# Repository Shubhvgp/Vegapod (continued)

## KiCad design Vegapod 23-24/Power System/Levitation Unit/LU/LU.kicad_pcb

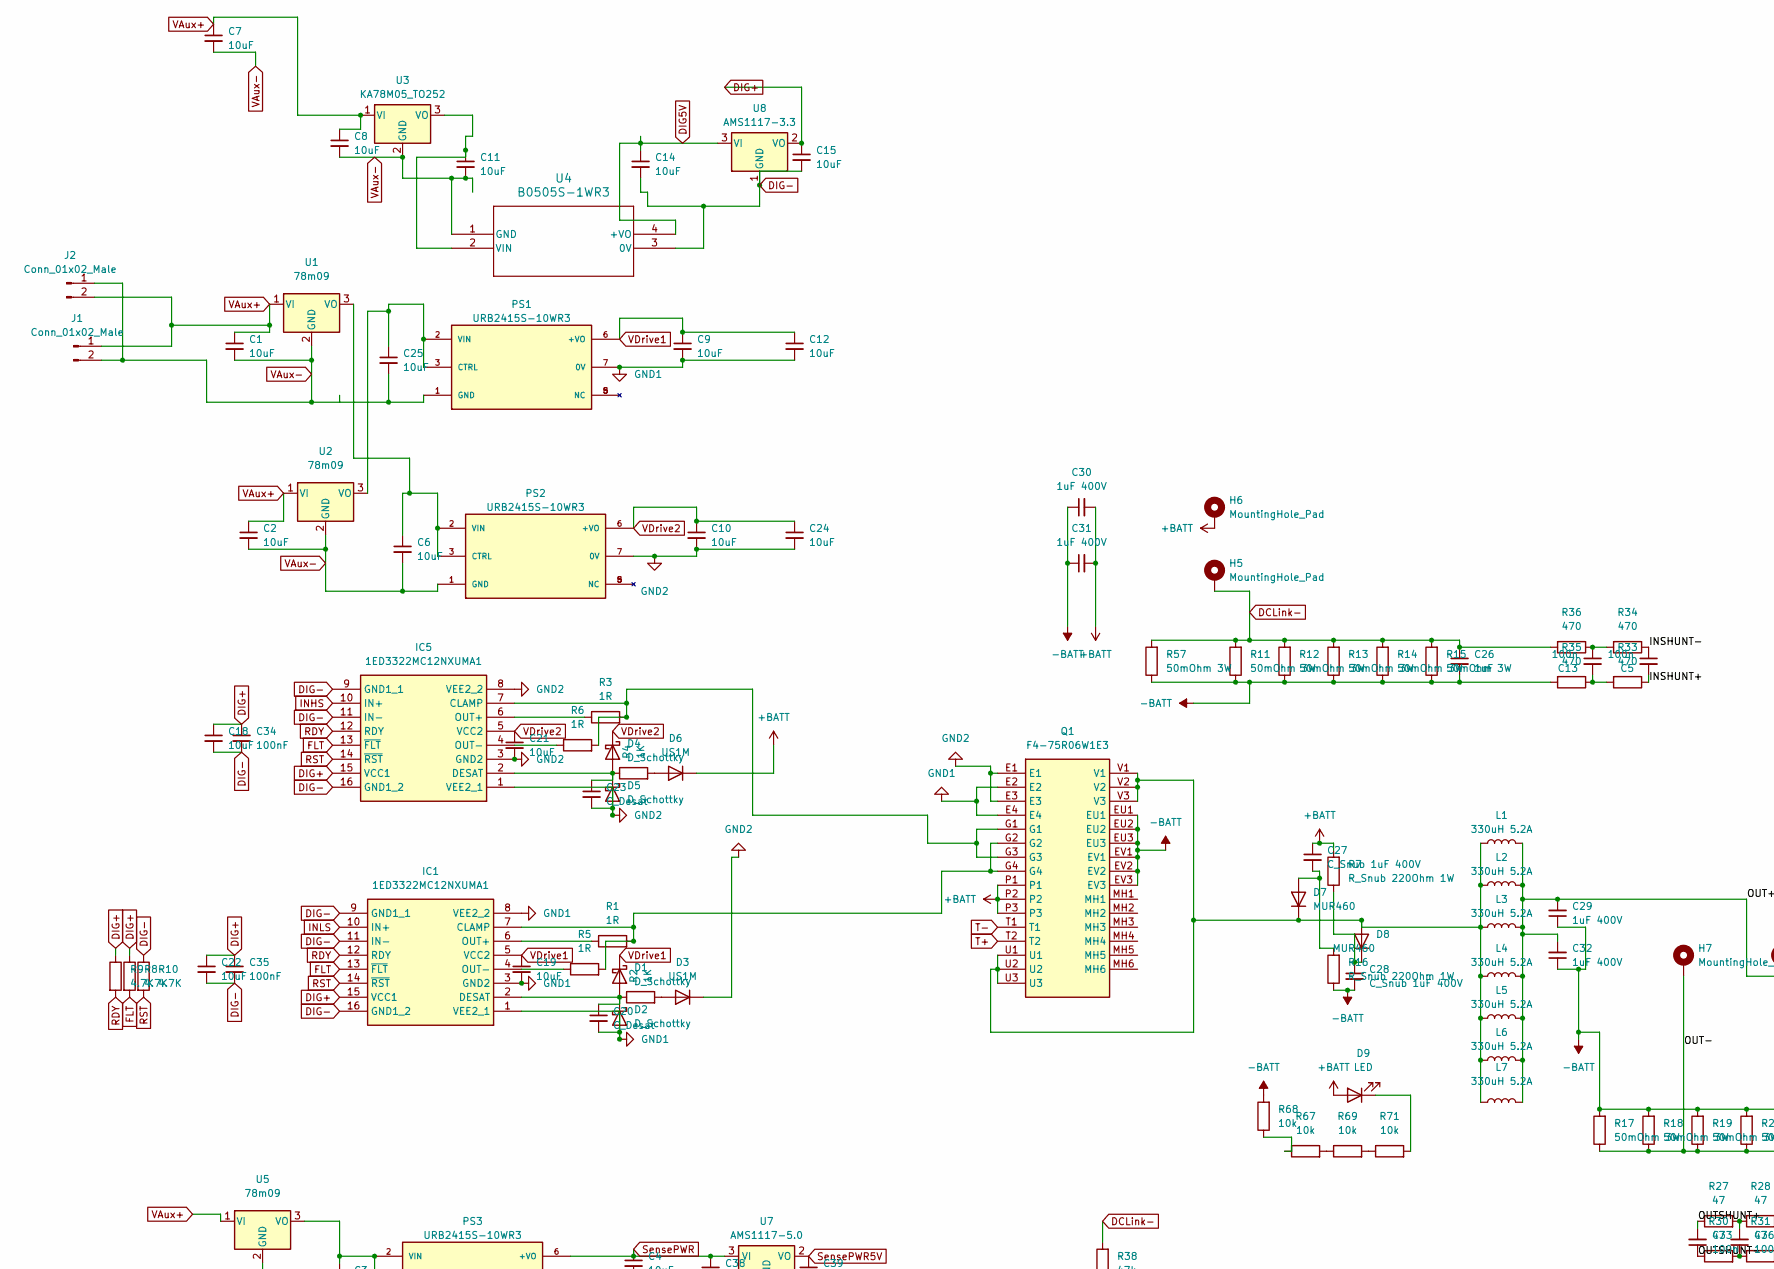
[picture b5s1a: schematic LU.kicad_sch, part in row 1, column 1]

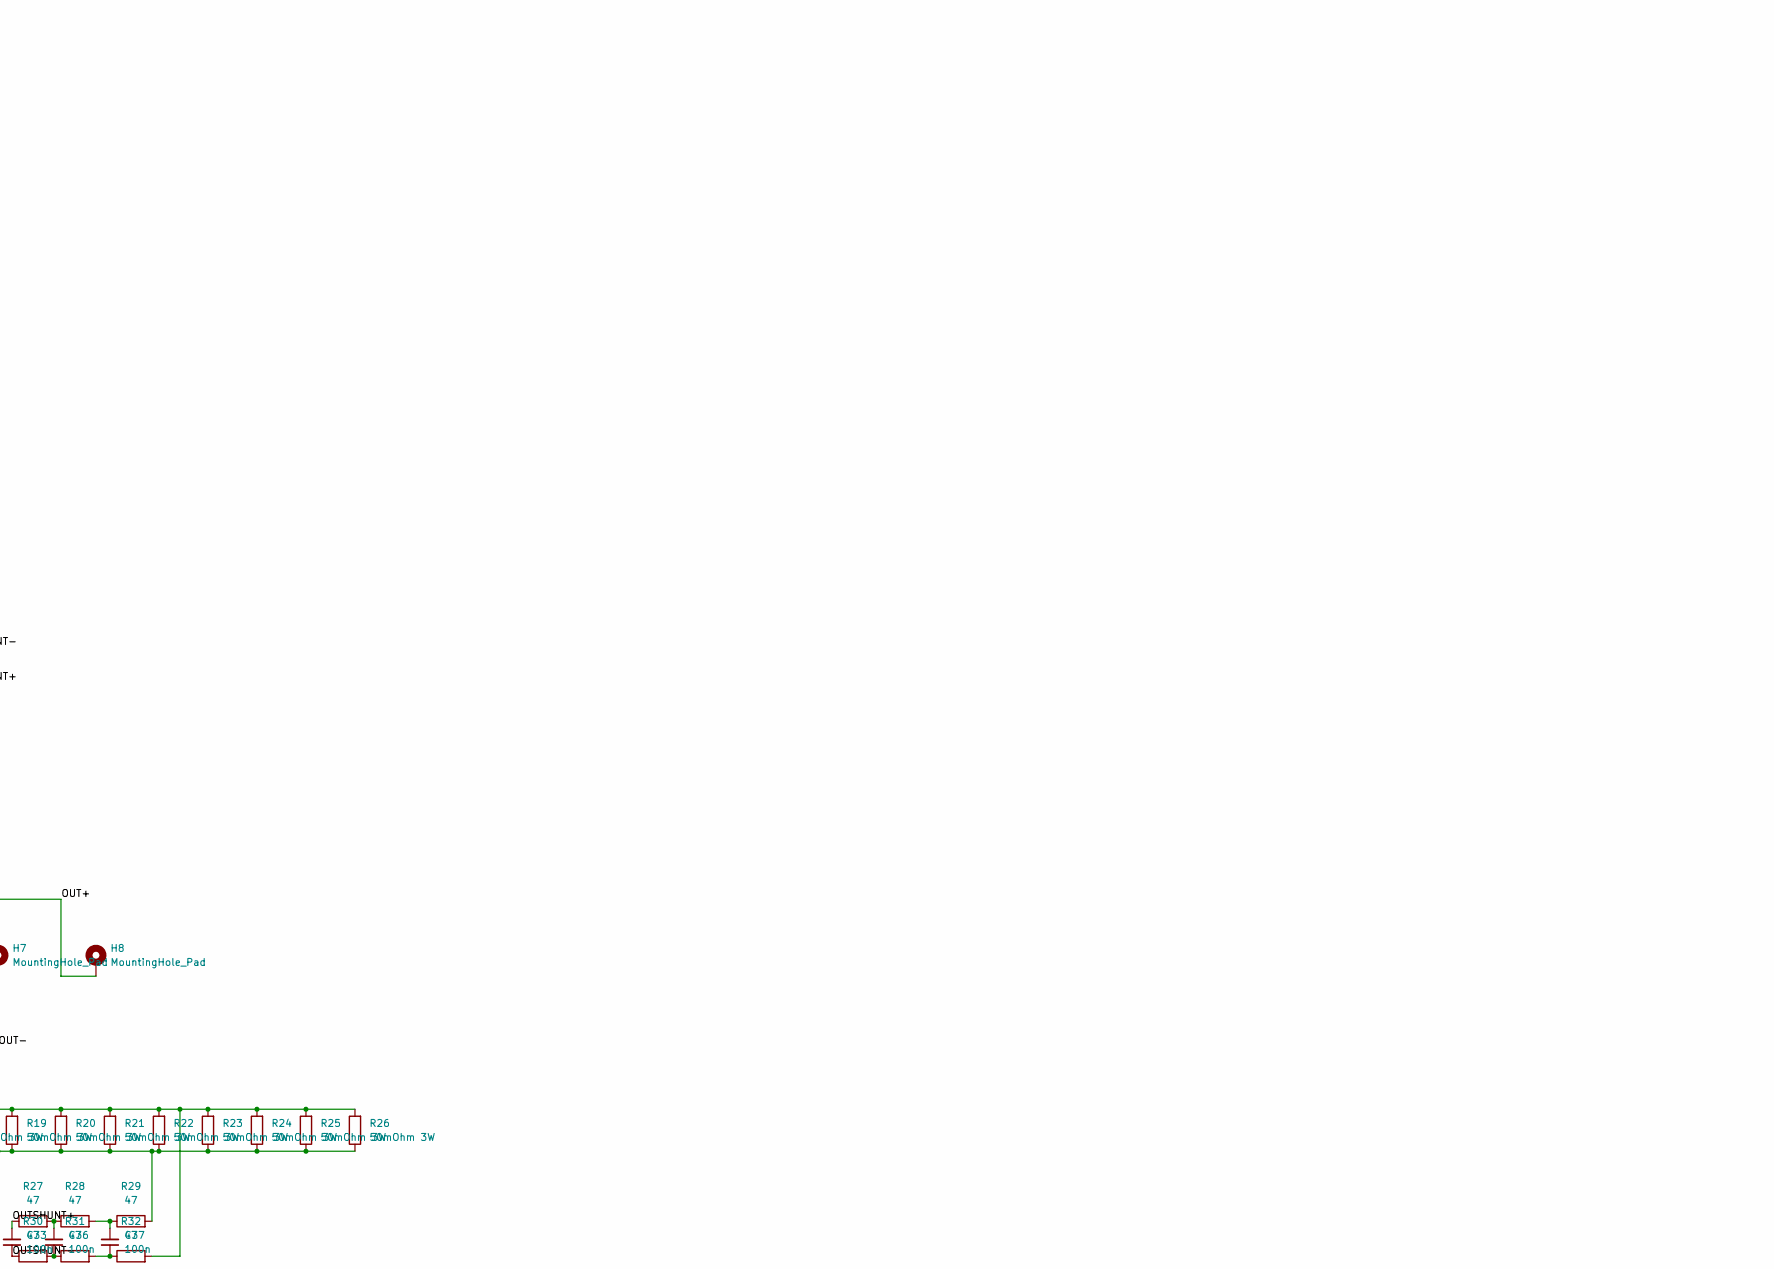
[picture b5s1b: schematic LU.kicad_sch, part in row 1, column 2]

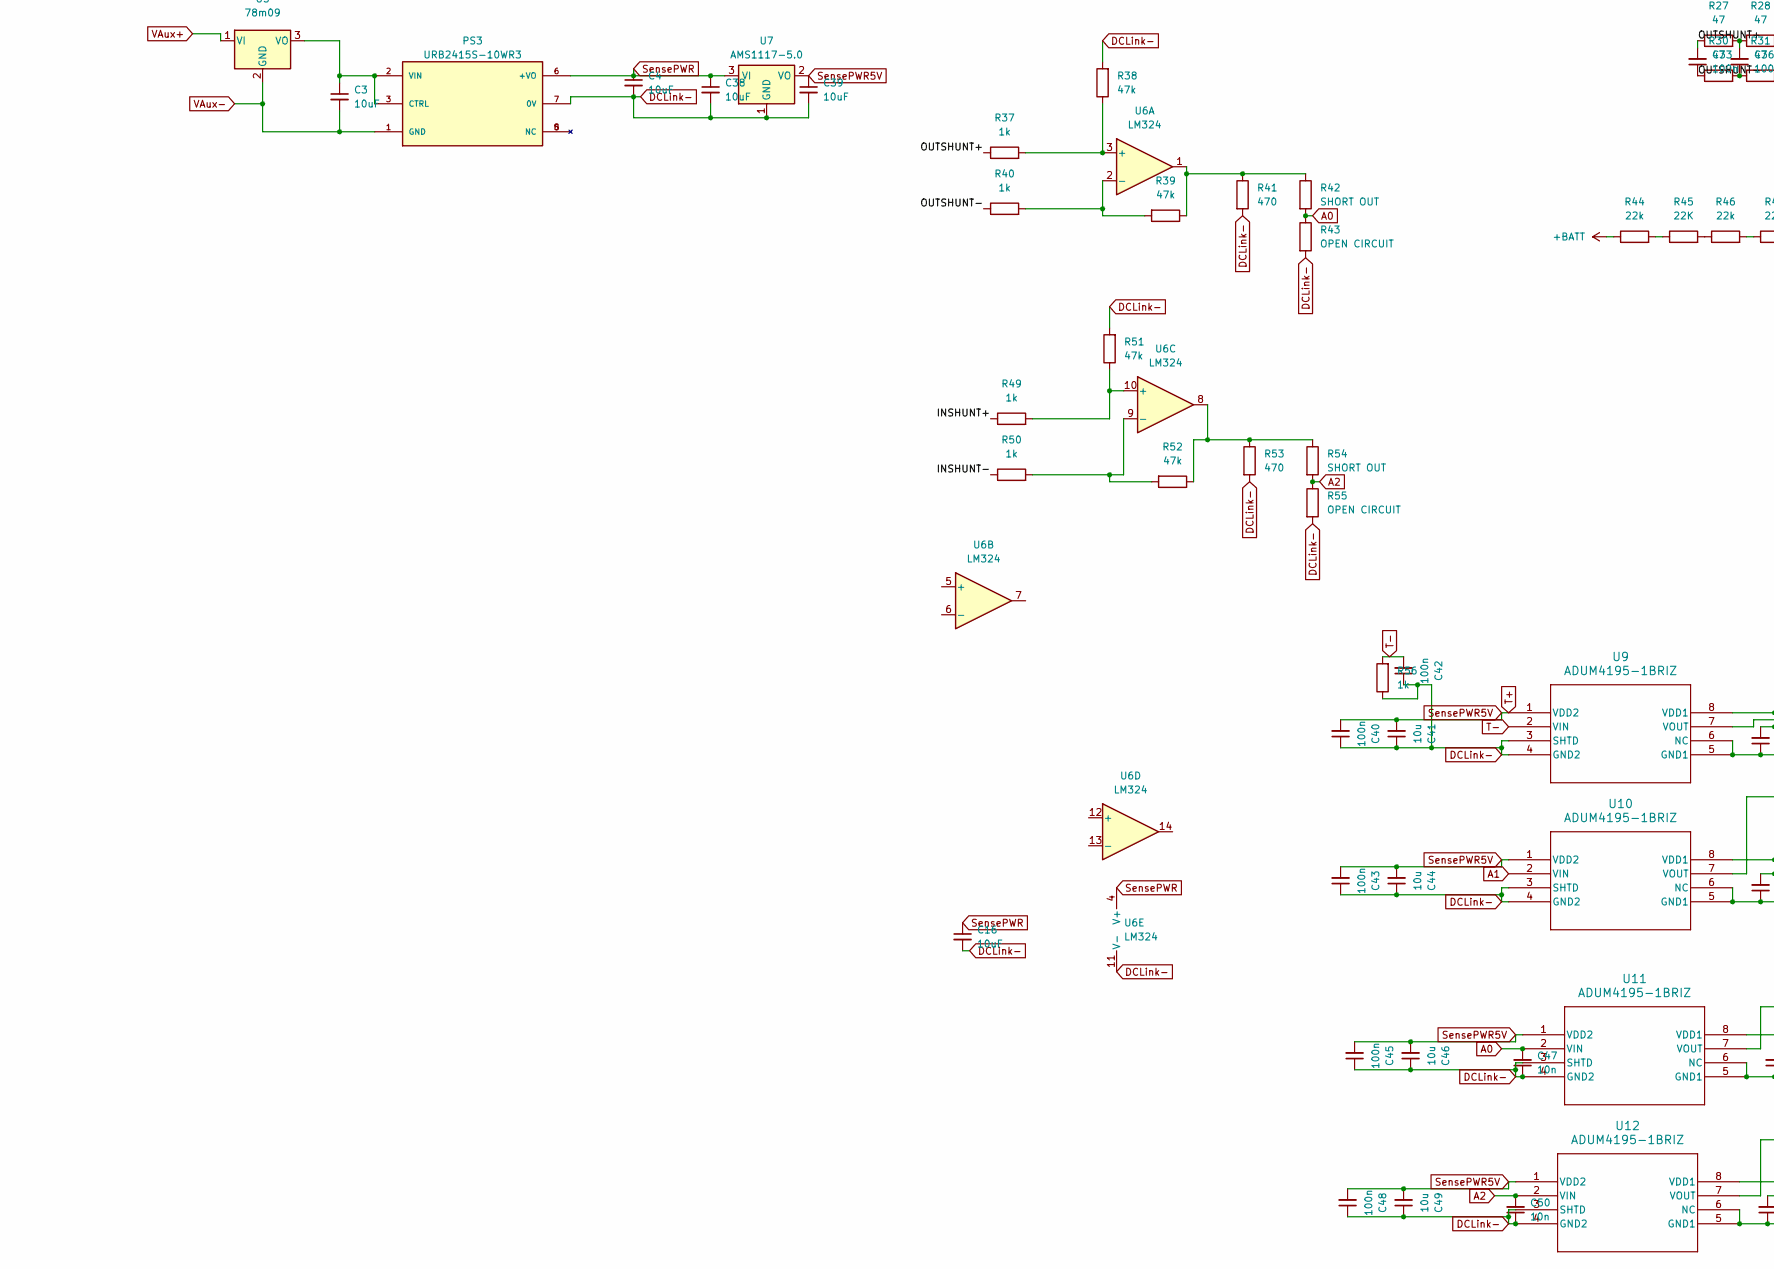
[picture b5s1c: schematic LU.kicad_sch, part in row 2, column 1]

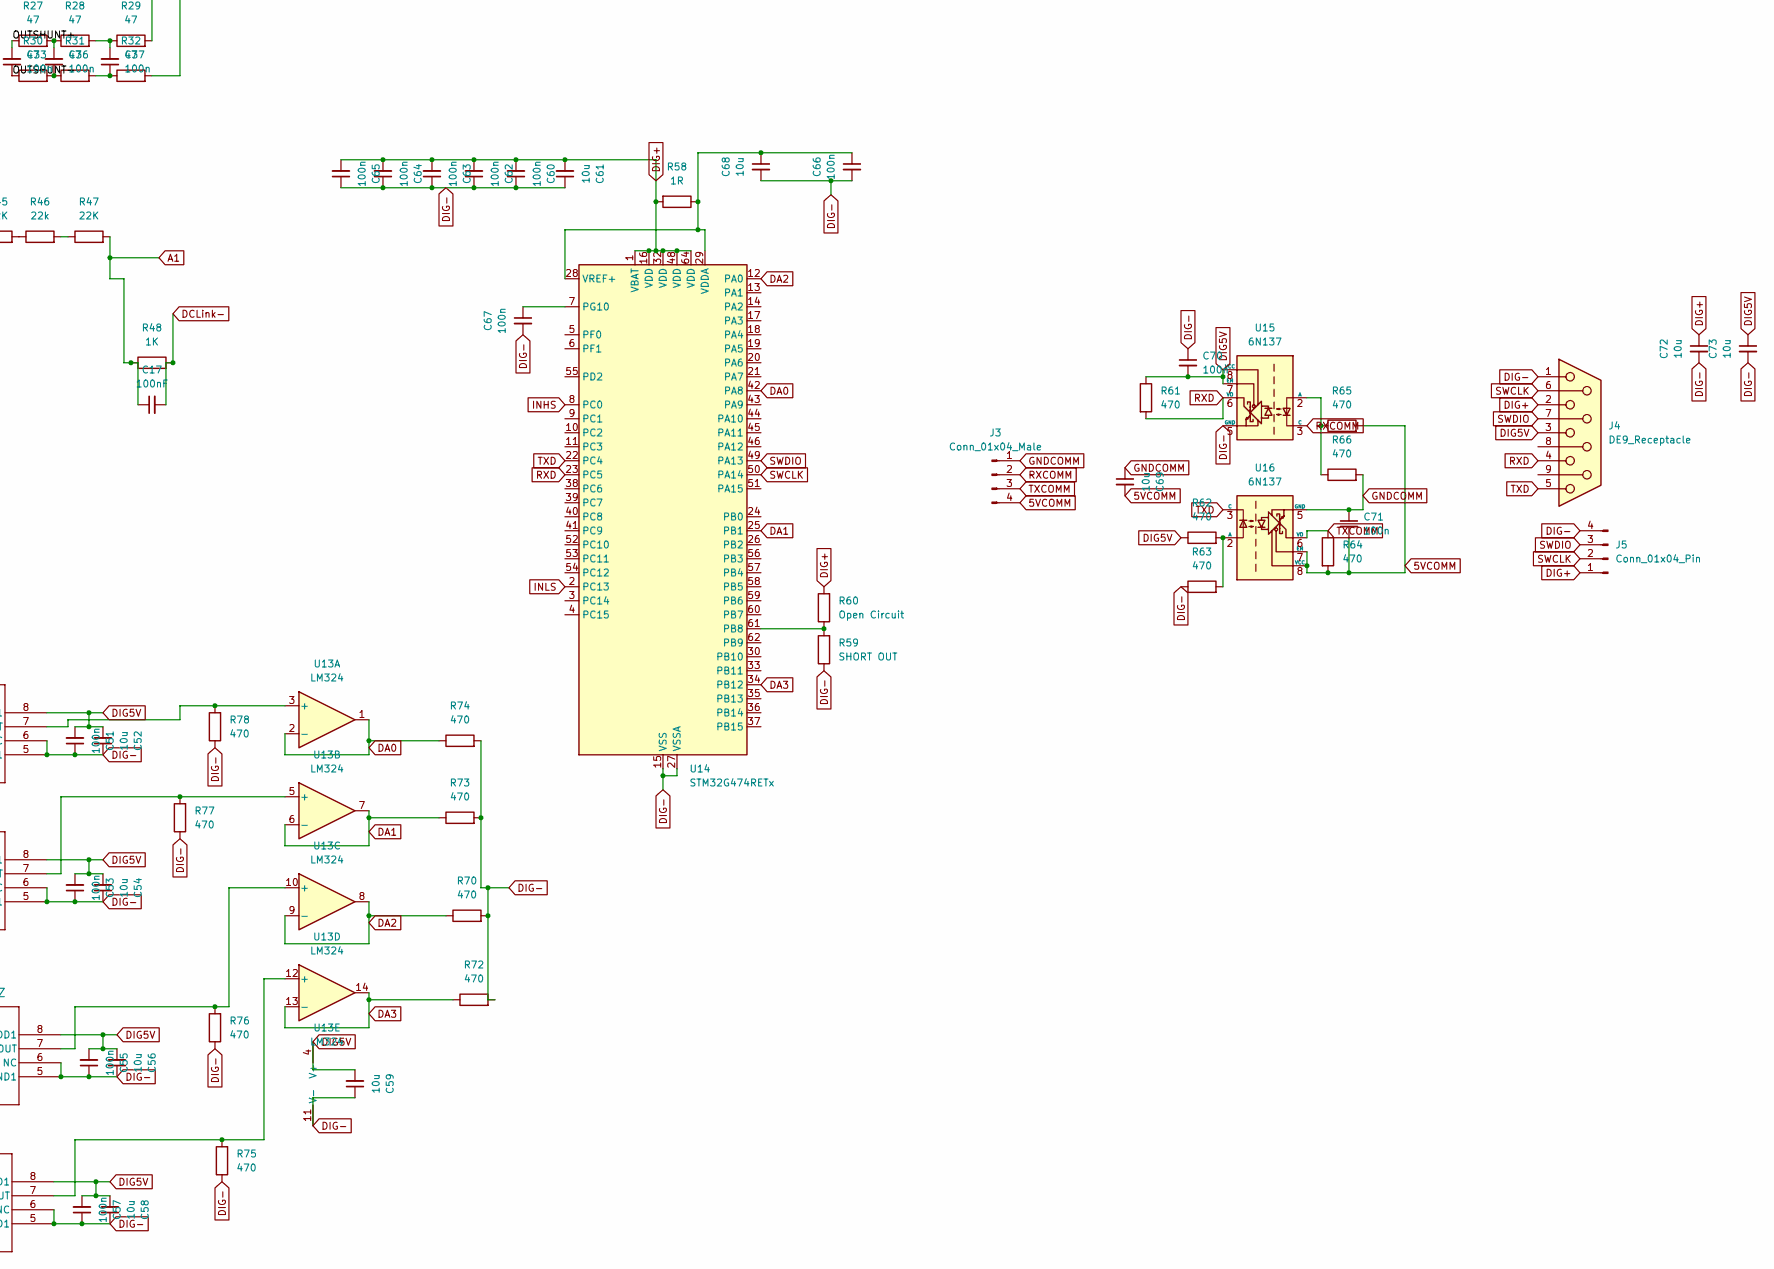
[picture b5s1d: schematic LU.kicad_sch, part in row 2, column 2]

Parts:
C1, C2, C3, C4, C6, C7, C8, C9, C10, C11, C12, C14, C15, C16, C18, C19, C21, C22, C24, C25, C38, C39: 10uF; C_1206_3216Metric_Pad1.33x1.80mm_HandSolder
C5, C13, C33, C36, C37, C40, C42, C43, C45, C48, C51, C53, C55, C57, C60, C62, C63, C64, C65, C66, C67, C70, C71: 100n; C_0805_2012Metric_Pad1.18x1.45mm_HandSolder
C17: 100nF; C_0805_2012Metric_Pad1.18x1.45mm_HandSolder
C20, C23: C_Desat; C_0603_1608Metric_Pad1.08x0.95mm_HandSolder
C26: 1uF; C_1206_3216Metric_Pad1.33x1.80mm_HandSolder
C27, C28: C_Snub 1uF 400V; C_Rect_L24.0mm_W8.3mm_P22.50mm_MKT
C29, C32: 1uF 400V; C_Rect_L19.0mm_W9.0mm_P15.00mm_MKS4
C30, C31: 1uF 400V; C_Rect_L24.0mm_W8.3mm_P22.50mm_MKT
C34, C35: 100nF; C_0603_1608Metric_Pad1.08x0.95mm_HandSolder
C41, C44, C46, C49, C52, C54, C56, C58, C59, C61, C68, C69, C72, C73: 10u; C_1206_3216Metric_Pad1.33x1.80mm_HandSolder
C47, C50: 10n; C_0805_2012Metric_Pad1.18x1.45mm_HandSolder
D1, D2, D4, D5: D_Schottky; D_SMA_Handsoldering
D3, D6: US1M; D_SMA_Handsoldering
D7, D8: MUR460; D_DO-201AE_P15.24mm_Horizontal
D9: LED; D_0805_2012Metric_Pad1.15x1.40mm_HandSolder
H5, H6: MountingHole_Pad; MountingHole_6.4mm_M6_DIN965_Pad
H7, H8: MountingHole_Pad; MountingHole_2.2mm_M2_DIN965_Pad
IC1, IC5: 1ED3322MC12NXUMA1; SOIC127P1030X265-16N; Mouser Part Number 726-1ED3322MC12NXUMA
J1: Conn_01x02_Male; JST_XH_B2B-XH-A_1x02_P2.50mm_Vertical
J2: Conn_01x02_Male; PinSocket_1x02_P2.54mm_Vertical
J3: Conn_01x04_Male; PinHeader_1x04_P2.54mm_Vertical
J4: DE9_Receptacle; DSUB-9_Male_Vertical_P2.77x2.84mm
J5: Conn_01x04_Pin; PinHeader_1x04_P1.27mm_Vertical
L1, L2, L3, L4, L5, L6, L7: 330uH 5.2A; L_Toroid_Vertical_L21.6mm_W11.4mm_P7.62mm_Pulse_KM-3
PS1, PS2, PS3: URB2415S-10WR3; CONV_URB2415S-10WR3; PARTREV 2020.11.09-A/4; DigiKey_Part_Number 2725-URB2415S-10WR3-ND
Q1: F4-75R06W1E3; F475R06W1E3; Mouser Part Number 641-F4-75R06W1E3
R1, R3, R5, R6, R58: 1R; R_0805_2012Metric_Pad1.20x1.40mm_HandSolder
R2, R4: 1K; R_0603_1608Metric_Pad0.98x0.95mm_HandSolder
R7, R16: R_Snub 220Ohm 1W; R_Box_L26.0mm_W5.0mm_P20.00mm
R8, R9, R10: 4.7K; R_0805_2012Metric_Pad1.20x1.40mm_HandSolder
R11, R12, R13, R14, R15, R17, R18, R19, R20, R21, R22, R23, R24, R25, R26, R57: 50mOhm 3W; R_2512_6332Metric_Pad1.40x3.35mm_HandSolder
R27, R28, R29, R30, R31, R32: 47; R_0805_2012Metric_Pad1.20x1.40mm_HandSolder
R33, R34, R35, R36, R41, R53, R61, R62, R63, R64, R65, R66, R70, R72, R73, R74, R75, R76, R77, R78: 470; R_0805_2012Metric_Pad1.20x1.40mm_HandSolder
R37, R40, R49, R50, R56: 1k; R_0805_2012Metric_Pad1.20x1.40mm_HandSolder
R38, R39, R51, R52: 47k; R_0805_2012Metric_Pad1.20x1.40mm_HandSolder
R42, R54: SHORT OUT; R_0805_2012Metric_Pad1.20x1.40mm_HandSolder
R43, R55: OPEN CIRCUIT; R_0805_2012Metric_Pad1.20x1.40mm_HandSolder
R44, R46: 22k; R_0805_2012Metric_Pad1.20x1.40mm_HandSolder
R45, R47: 22K; R_0805_2012Metric_Pad1.20x1.40mm_HandSolder
R48: 1K; R_0805_2012Metric_Pad1.20x1.40mm_HandSolder
R59: SHORT OUT; R_0402_1005Metric
R60: Open Circuit; R_0402_1005Metric
R67, R68, R69, R71: 10k; R_0805_2012Metric_Pad1.20x1.40mm_HandSolder
U1, U2, U5: 78m09; TO-252-2
U3: KA78M05_TO252; TO-252-2
U4: B0505S-1WR3; B0505S_MNS
U6, U13: LM324; SOIC-14_3.9x8.7mm_P1.27mm
U7: AMS1117-5.0; SOT-223-3_TabPin2
U8: AMS1117-3.3; SOT-223-3_TabPin2
U9, U10, U11, U12: ADUM4195-1BRIZ; RI-8-1_ADI
U14: STM32G474RETx; LQFP-64_10x10mm_P0.5mm
U15, U16: 6N137; SSO-8_6.7x9.8mm_P2.54mm_Clearance8mm

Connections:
5VCOMM: C69.2, C71.2, J3.4, R64.2, R65.2, U16.7 (EN), U16.8 (VCC)
+BATT: C27.1, C30.2, C31.2, D6.1 (K), D9.2 (A), H6.1, Q1.P1, Q1.P2, Q1.P3, R7.2, R44.1
-BATT: C26.2, C28.2, C29.1, C30.1, C31.1, C32.1, Q1.EU1, Q1.EU2, Q1.EU3, Q1.EV1, Q1.EV2, Q1.EV3, R11.1, R12.1, R13.1, R14.1, R15.1, R16.1, R17.2, R18.2, R19.2, R20.2, R21.2, R22.2, R23.2, R24.2, R25.2, R26.2, R32.2, R35.2, R57.1, R68.2
/INSHUNT+: C5.2, R33.1, R49.1
/INSHUNT-: C5.1, R34.1, R50.1
/OUT+: C29.2, C32.2, H8.1, L1.2, L2.2, L3.2, L4.2, L5.2, L6.2, L7.2
/OUT-: H7.1, R17.1, R18.1, R19.1, R20.1, R21.1, R22.1, R23.1, R24.1, R25.1, R26.1, R29.2
/OUTSHUNT+: C33.2, R27.1, R37.1
/OUTSHUNT-: C33.1, R30.1, R40.1
A0: C47.2, R42.2, R43.1, U11.2 (VIN)
A1: C17.1, R47.2, R48.1, U10.2 (VIN)
A2: C50.2, R54.2, R55.1, U12.2 (VIN)
DA0: R74.1, U13.1, U13.2 (-), U14.42 (PA8)
DA1: R73.1, U13.6 (-), U13.7, U14.25 (PB1)
DA2: R70.1, U13.8, U13.9 (-), U14.12 (PA0)
DA3: R72.1, U13.13 (-), U13.14, U14.34 (PB12)
DCLink-: C4.2, C16.2, C17.2, C26.1, C38.2, C39.2, C40.1, C41.1, C42.1, C43.1, C44.1, C45.1, C46.1, C47.1, C48.1, C49.1, C50.1, H5.1, PS3.7 (0V), R11.2, R12.2, R13.2, R14.2, R15.2, R36.2, R38.2, R41.2, R43.2, R48.2, R51.2, R53.2, R55.2, R56.1, R57.2, U6.11 (V-), U7.1 (GND), U9.3 (SHTD), U9.4 (GND2), U10.3 (SHTD), U10.4 (GND2), U11.3 (SHTD), U11.4 (GND2), U12.3 (SHTD), U12.4 (GND2)
DIG5V: C14.1, C51.2, C52.2, C53.2, C54.2, C55.2, C56.2, C57.2, C58.2, C59.2, C70.2, C73.1, J4.3, R61.1, R62.1, U4.4 (+VO), U8.3 (VI), U9.8 (VDD1), U10.8 (VDD1), U11.8 (VDD1), U12.8 (VDD1), U13.4 (V+), U15.7 (EN), U15.8 (VCC)
DIG+: C15.1, C18.1, C22.1, C34.1, C35.1, C60.2, C61.2, C62.2, C63.2, C64.2, C65.2, C72.1, IC1.15 (VCC1), IC5.15 (VCC1), J4.2, J5.1, R8.1, R9.1, R58.2, R60.2, U8.2 (VO), U14.1 (VBAT), U14.16 (VDD), U14.32 (VDD), U14.48 (VDD), U14.64 (VDD)
DIG-: C14.2, C15.2, C18.2, C22.2, C34.2, C35.2, C51.1, C52.1, C53.1, C54.1, C55.1, C56.1, C57.1, C58.1, C59.1, C60.1, C61.1, C62.1, C63.1, C64.1, C65.1, C66.2, C67.2, C68.2, C70.1, C72.2, C73.2, IC1.9 (GND1_1), IC1.11 (IN-), IC1.16 (GND1_2), IC5.9 (GND1_1), IC5.11 (IN-), IC5.16 (GND1_2), J4.1, J5.4, R10.1, R59.1, R63.1, R70.2, R72.2, R73.2, R74.2, R75.1, R76.1, R77.1, R78.1, U4.3 (0V), U8.1 (GND), U9.5 (GND1), U9.6 (NC), U10.5 (GND1), U10.6 (NC), U11.5 (GND1), U11.6 (NC), U12.5 (GND1), U12.6 (NC), U13.11 (V-), U14.15 (VSS), U14.27 (VSSA), U14.31 (VSS), U14.47 (VSS), U14.63 (VSS), U15.5 (GND)
FLT: IC1.13 (~FLT), IC5.13 (~FLT), R8.2
GND1: C9.2, C12.2, C19.2, C20.2, D2.2 (A), IC1.1 (VEE2_1), IC1.3 (GND2), IC1.8 (VEE2_2), PS1.7 (0V), Q1.E2, Q1.E4
GND2: C10.2, C21.2, C23.2, C24.2, D3.1 (K), D5.2 (A), IC5.1 (VEE2_1), IC5.3 (GND2), IC5.8 (VEE2_2), PS2.7 (0V), Q1.E1, Q1.E3
GNDCOMM: C69.1, C71.1, J3.1, R66.2, U16.5 (GND)
INHS: IC5.10 (IN+), U14.8 (PC0)
INLS: IC1.10 (IN+), U14.2 (PC13)
unnamed: C13.1, R34.2, R36.1
unnamed: C13.2, R33.2, R35.1
unnamed: C36.1, R30.2, R31.1
unnamed: C36.2, R27.2, R28.1
unnamed: C37.1, R31.2, R32.1
unnamed: C37.2, R28.2, R29.1
unnamed: C20.1, D1.2 (A), D2.1 (K), IC1.2 (DESAT), R2.1
unnamed: D3.2 (A), R2.2
unnamed: C23.1, D4.2 (A), D5.1 (K), IC5.2 (DESAT), R4.1
unnamed: D6.2 (A), R4.2
unnamed: C27.2, D7.2 (A), R16.2
unnamed: D7.1 (K), D8.2 (A), L1.1, L2.1, L3.1, L4.1, L5.1, L6.1, L7.1, Q1.U1, Q1.U2, Q1.U3, Q1.V1, Q1.V2, Q1.V3
unnamed: C28.1, D8.1 (K), R7.1
unnamed: D9.1 (K), R71.2
unnamed: IC1.7 (CLAMP), Q1.G2, Q1.G4, R1.2, R5.2
unnamed: IC1.6 (OUT+), R1.1
unnamed: IC1.4 (OUT-), R5.1
unnamed: IC5.7 (CLAMP), Q1.G1, Q1.G3, R3.2, R6.2
unnamed: IC5.6 (OUT+), R3.1
unnamed: IC5.4 (OUT-), R6.1
unnamed: C25.1, PS1.2 (VIN), PS1.3 (CTRL), U2.3 (VO)
unnamed: C6.1, PS2.2 (VIN), PS2.3 (CTRL), U1.3 (VO)
unnamed: C3.1, PS3.2 (VIN), PS3.3 (CTRL), U5.3 (VO)
unnamed: R39.1, R41.1, R42.1, U6.1
unnamed: R44.2, R45.1
unnamed: R45.2, R46.1
unnamed: R46.2, R47.1
unnamed: R52.1, R53.1, R54.1, U6.8
unnamed: R67.1, R68.1
unnamed: R67.2, R69.1
unnamed: R69.2, R71.1
unnamed: C11.1, U3.3 (VO), U4.2 (VIN)
unnamed: R37.2, R38.1, U6.3 (+)
unnamed: R39.2, R40.2, U6.2 (-)
unnamed: R49.2, R51.1, U6.10 (+)
unnamed: R50.2, R52.2, U6.9 (-)
unnamed: R77.2, U10.7 (VOUT), U13.5 (+)
unnamed: R76.2, U11.7 (VOUT), U13.10 (+)
unnamed: R75.2, U12.7 (VOUT), U13.12 (+)
unnamed: R78.2, U9.7 (VOUT), U13.3 (+)
unnamed: R59.2, R60.1, U14.61 (PB8)
unnamed: C67.1, U14.7 (PG10)
unnamed: C66.1, C68.1, R58.1, U14.28 (VREF+), U14.29 (VDDA)
unnamed: R65.1, R66.1, U15.2 (A)
unnamed: R62.2, R63.2, U16.2 (A)
RDY: IC1.12 (RDY), IC5.12 (RDY), R9.2
RST: IC1.14 (~RST), IC5.14 (~RST), R10.2
RXCOMM: J3.2, U15.3 (C)
RXD: J4.4, R61.2, U14.23 (PC5), U15.6 (VO)
SWCLK: J4.6, J5.2, U14.50 (PA14)
SWDIO: J4.7, J5.3, U14.49 (PA13)
SensePWR: C4.1, C16.1, C38.1, PS3.6 (+VO), U6.4 (V+), U7.3 (VI)
SensePWR5V: C39.1, C40.2, C41.2, C43.2, C44.2, C45.2, C46.2, C48.2, C49.2, Q1.T2, U7.2 (VO), U9.1 (VDD2), U10.1 (VDD2), U11.1 (VDD2), U12.1 (VDD2)
T-: C42.2, Q1.T1, R56.2, U9.2 (VIN)
TXCOMM: J3.3, R64.1, U16.6 (VO)
TXD: J4.5, U14.22 (PC4), U16.3 (C)
VAux+: C1.1, C2.1, C7.1, C8.1, J1.1, J2.2, U1.1 (VI), U2.1 (VI), U3.1 (VI), U5.1 (VI)
VAux-: C1.2, C2.2, C3.2, C6.2, C7.2, C8.2, C11.2, C25.2, J1.2, J2.1, PS1.1 (GND), PS2.1 (GND), PS3.1 (GND), U1.2 (GND), U2.2 (GND), U3.2 (GND), U4.1 (GND), U5.2 (GND)
VDrive1: C9.1, C12.1, C19.1, D1.1 (K), IC1.5 (VCC2), PS1.6 (+VO)
VDrive2: C10.1, C21.1, C24.1, D4.1 (K), IC5.5 (VCC2), PS2.6 (+VO)

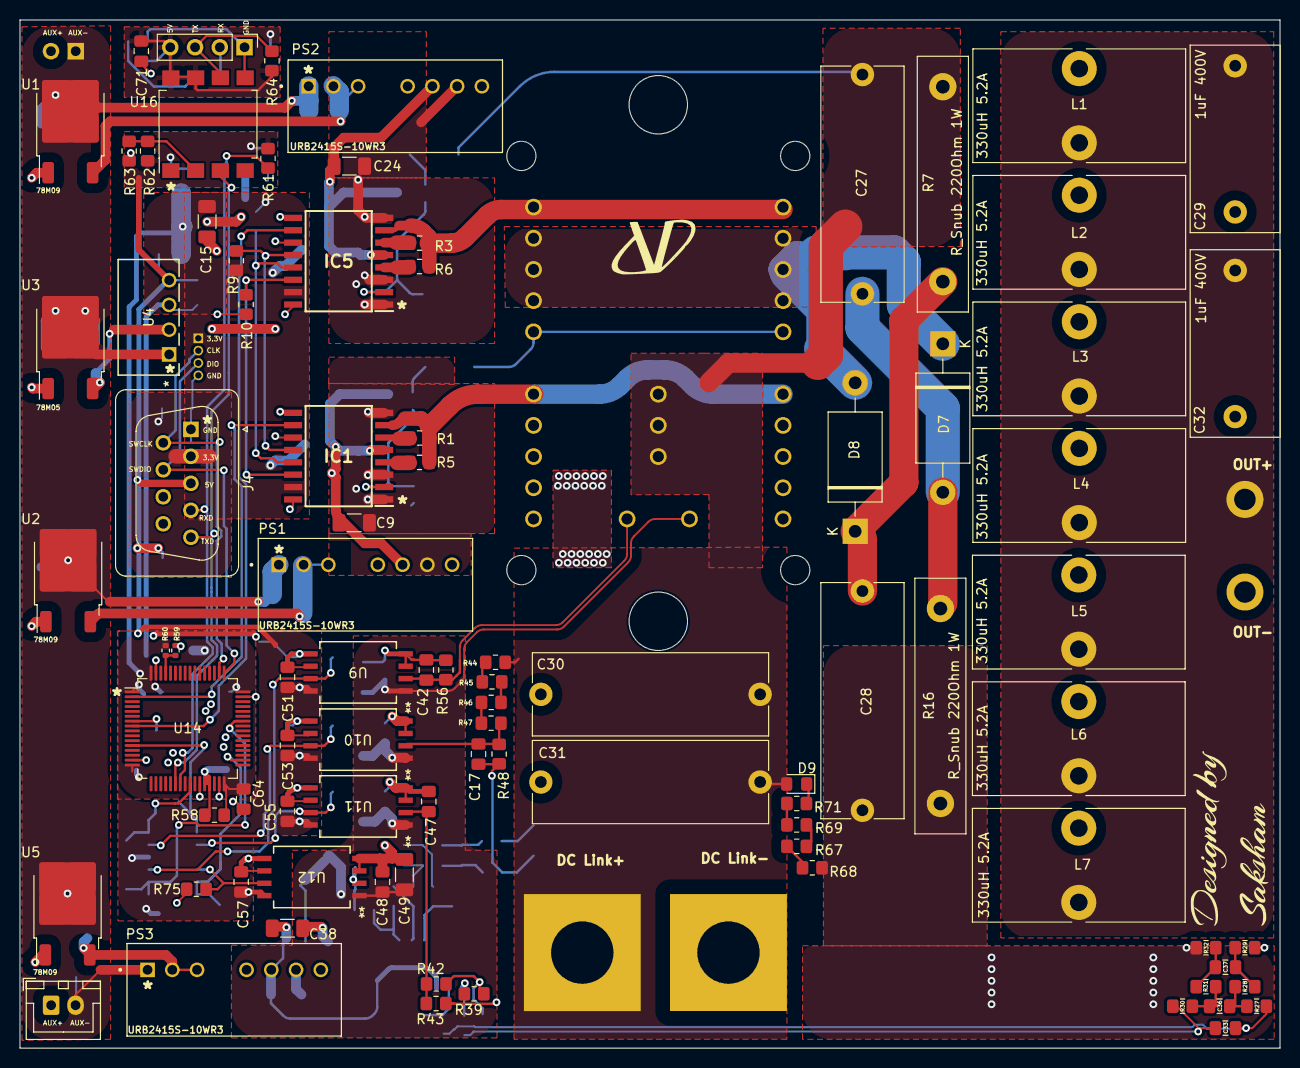
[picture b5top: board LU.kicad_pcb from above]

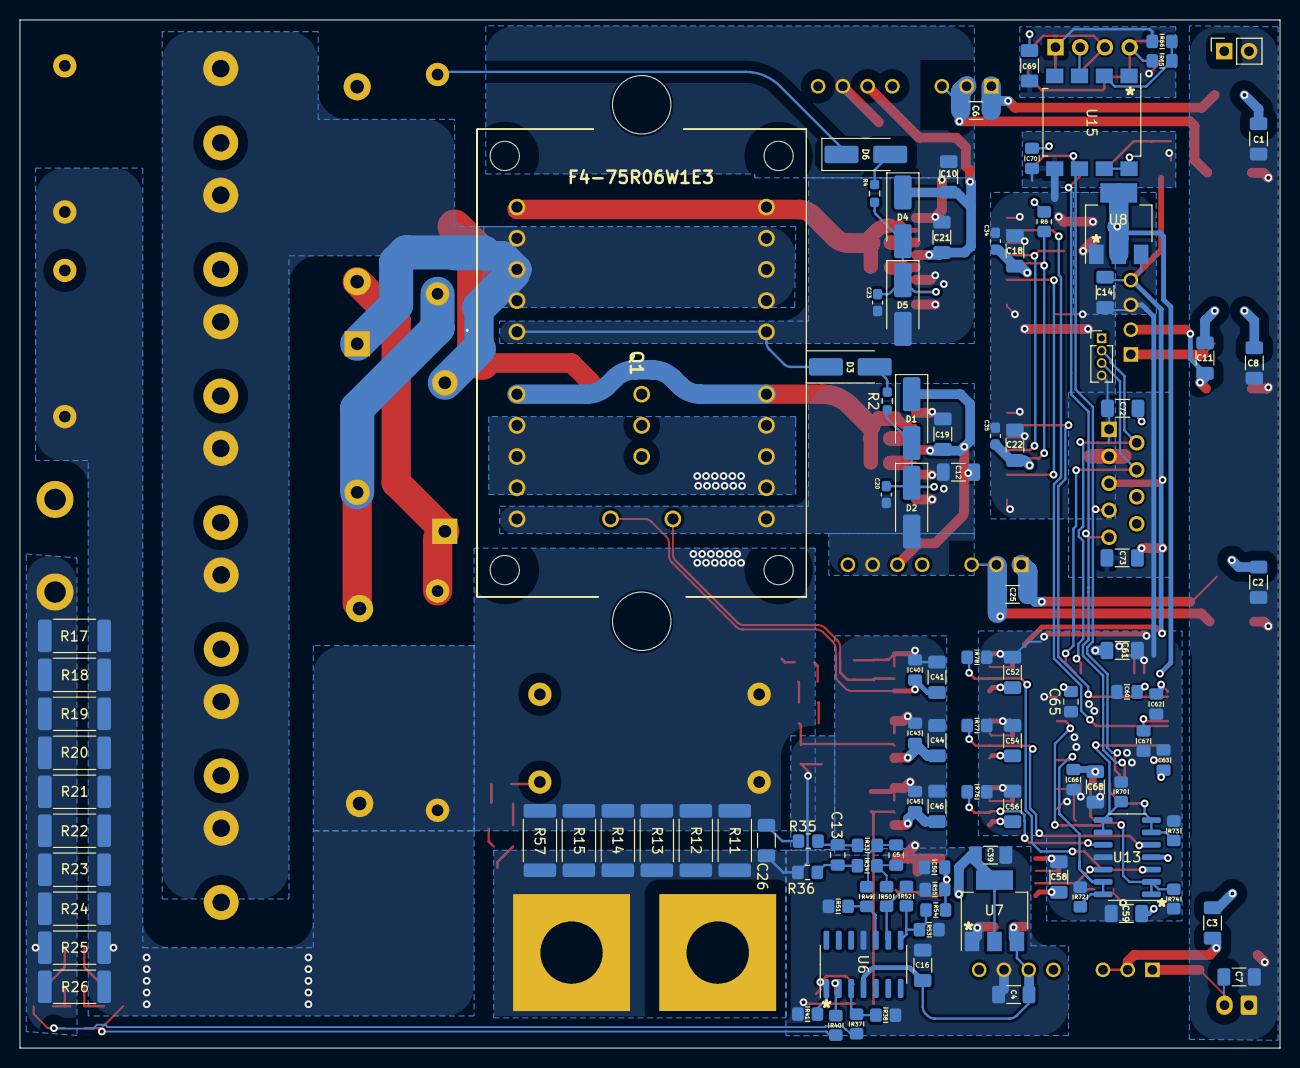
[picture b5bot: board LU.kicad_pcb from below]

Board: 2 copper layers, 129.3 x 105.5 mm, 198 parts (106 on the bottom side), 86 nets.

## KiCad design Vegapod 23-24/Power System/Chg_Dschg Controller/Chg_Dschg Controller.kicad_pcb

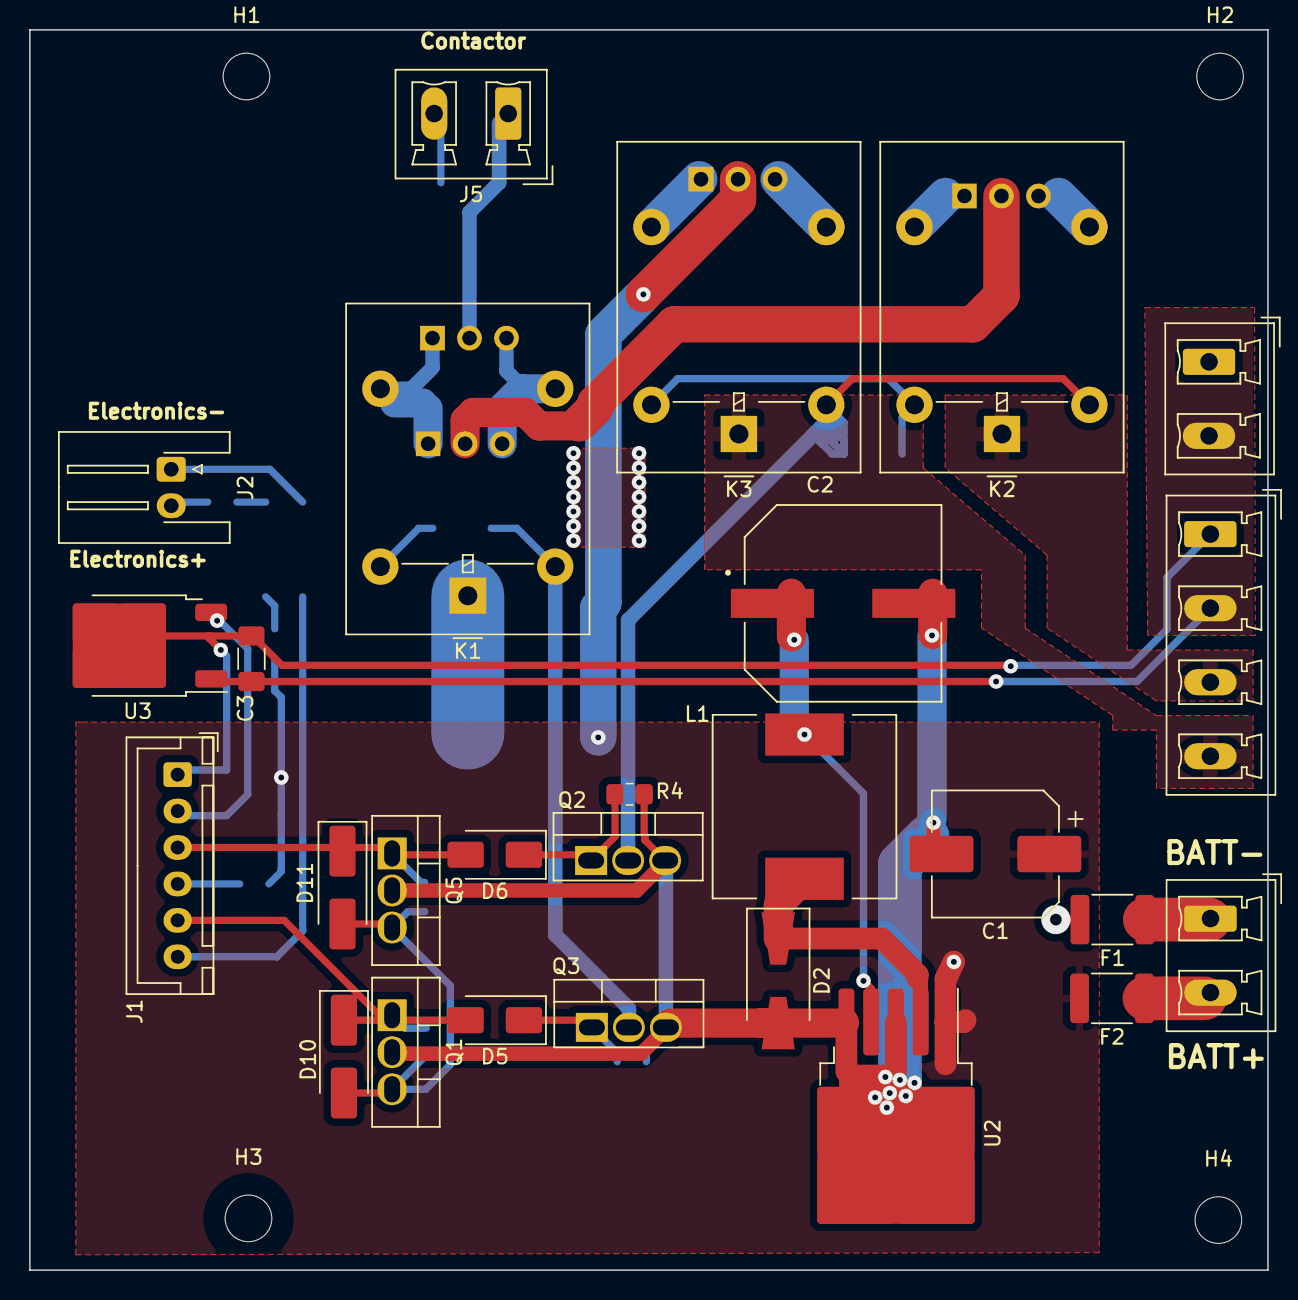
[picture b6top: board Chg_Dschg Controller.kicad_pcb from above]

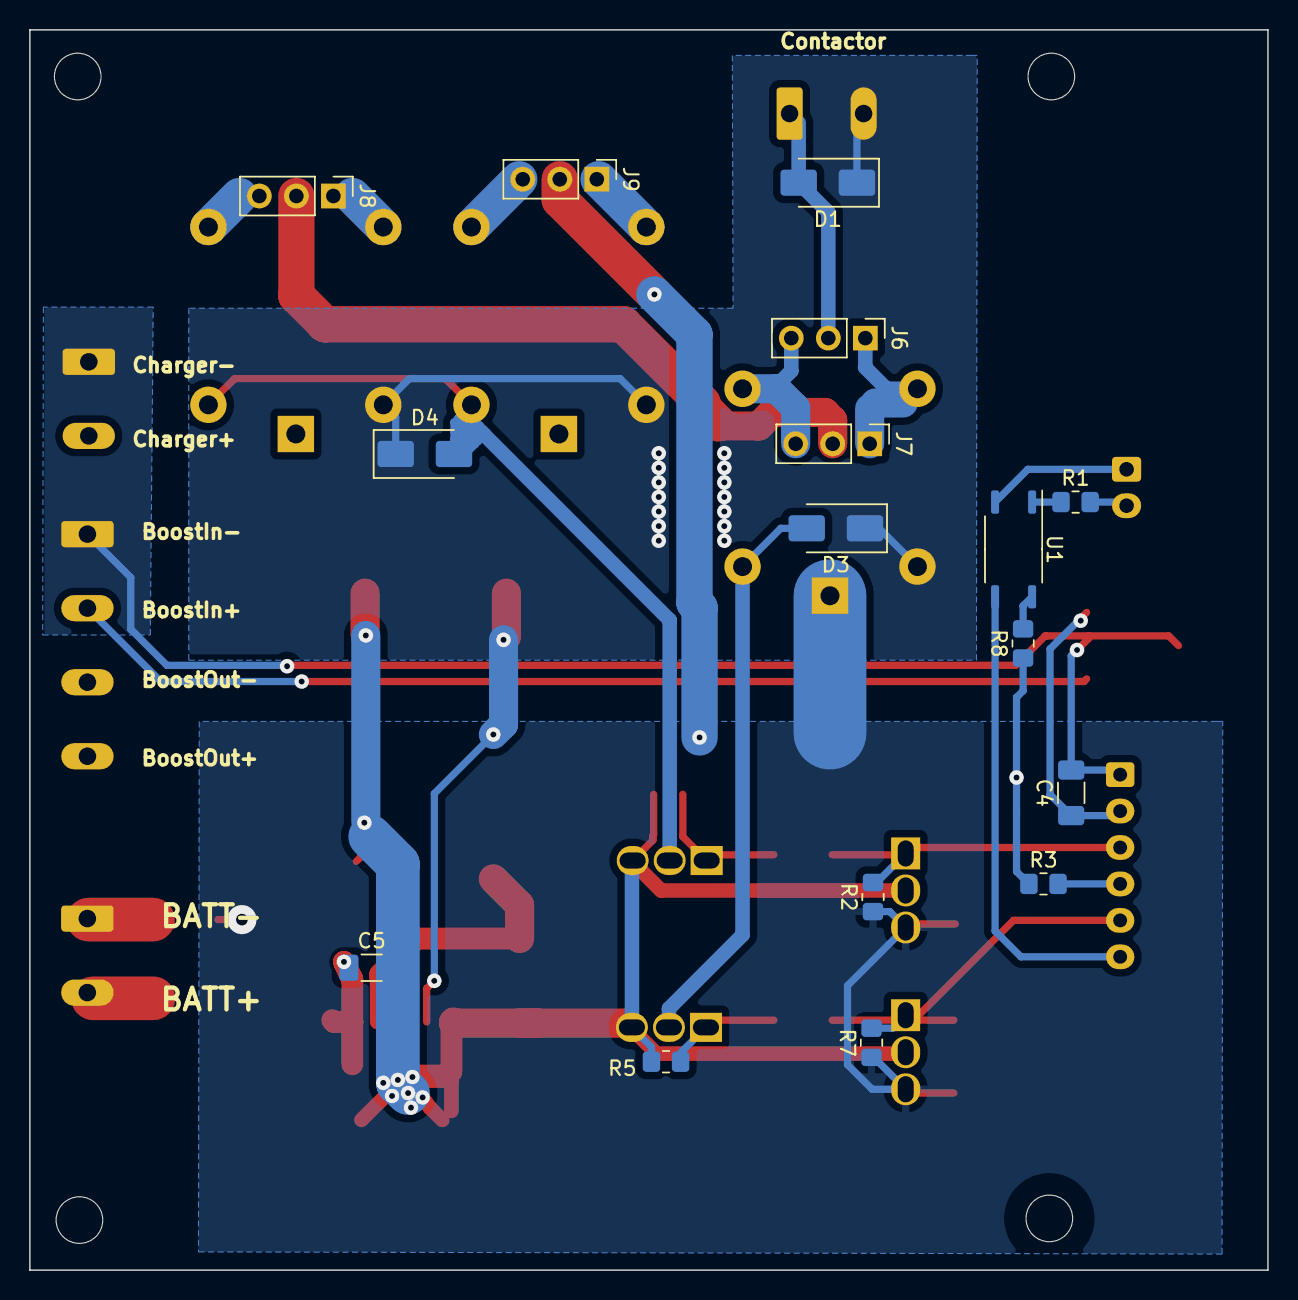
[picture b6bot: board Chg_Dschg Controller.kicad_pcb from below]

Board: 2 copper layers, 85.0 x 85.1 mm, 47 parts (16 on the bottom side), 32 nets.

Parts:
C1: 100uF 50V; CP_Elec_8x10.5
C2: 25V 1000uF; CAP_EEEFK1E102AQ
C3, C4, C5: 1uF; C_1206_3216Metric_Pad1.33x1.80mm_HandSolder
D1, D3, D4, D5, D6: 1n4007; D_SMA
D2: SS56; D_SMA-SMB_Universal_Handsoldering
D10, D11: D_Zener; D_SMA_Handsoldering
F1, F2: 5A 1808; R_1812_4532Metric_Pad1.30x3.40mm_HandSolder
H1, H2, H3, H4: MountingHole; MountingHole_3.2mm_M3
J1: Slave socket; JST_XH_B6B-XH-A_1x06_P2.50mm_Vertical
J2: Electronics; JST_XH_S2B-XH-A-1_1x02_P2.50mm_Horizontal
J3: Charger; PhoenixContact_MCV_1,5_2-G-5.08_1x02_P5.08mm_Vertical
J4: Battery; PhoenixContact_MCV_1,5_2-G-5.08_1x02_P5.08mm_Vertical
J5: Contactor; PhoenixContact_MCV_1,5_2-G-5.08_1x02_P5.08mm_Vertical
J6: NO/NC Contactor; PinHeader_1x03_P2.54mm_Vertical
J7: NC/NO Charge; PinHeader_1x03_P2.54mm_Vertical
J8: NO/NC Charge-; PinHeader_1x03_P2.54mm_Vertical
J9: NO/NC Charge+; PinHeader_1x03_P2.54mm_Vertical
J10: Conn_01x04_Pin; PhoenixContact_MCV_1,5_4-G-5.08_1x04_P5.08mm_Vertical
K1, K2, K3: Relay_SPDT; Relay_SPDT_Omron-G5LE-1
L1: CDRH127 100u; L_12x12mm_H8mm
Q1, Q2, Q3, Q5: IRLZ44N; TO-220-3_Vertical
R1: 470; R_0805_2012Metric_Pad1.20x1.40mm_HandSolder
R2, R3, R7, R8: 10k; R_0805_2012Metric_Pad1.20x1.40mm_HandSolder
R4, R5: 100k; R_0805_2012Metric_Pad1.20x1.40mm_HandSolder
U1: TLP185; SOIC-4_4.55x3.7mm_P2.54mm
U2: LM2576HVS-12; TO-263-5_TabPin3
U3: LM78M05_TO252; TO-252-2

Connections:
+BATT: C1.1, C5.1, F2.2, J9.2, R3.1, R8.1, U2.1 (VIN)
-BATT: D10.2 (A), D11.2 (A), F1.2, K1.1, Q1.3 (S), Q5.3 (S), R2.1, R7.1
/5V: C4.1, J1.2, U3.3 (VO)
/12V: C2.1, D1.1 (K), D3.1 (K), D4.1 (K), J5.2, K1.5, K2.5, K3.5, L1.2, U2.4 (FB)
/NCR1: J6.1, J7.1, K1.4
/NOR1: J6.3, J7.3, K1.3
BOOSTIN+: C3.1, J3.2, J10.2, U3.1 (VI)
BOOSTIN-: C3.2, C4.2, J1.1, J3.1, J10.1, U3.2 (GND)
BOOSTOUT+: J10.4, K3.1
BOOSTOUT-: J10.3, K2.1
unnamed: D1.2 (A), J5.1, J6.2
unnamed: C1.2, C2.2, C5.2, D2.2 (A), Q1.2 (D), Q2.3 (S), Q3.3 (S), Q5.2 (D), R4.1, R5.1, U2.3 (GND), U2.5 (~ON/OFF)
unnamed: D2.1 (K), L1.1, U2.2 (OUT)
unnamed: D3.2 (A), K1.2, Q3.2 (D)
unnamed: D4.2 (A), K2.2, K3.2, Q2.2 (D)
unnamed: D5.1 (K), Q3.1 (G), R5.2
unnamed: D6.1 (K), Q2.1 (G), R4.2
unnamed: D5.2 (A), D10.1 (K), J1.5, Q1.1 (G), R7.2
unnamed: D6.2 (A), D11.1 (K), J1.3, Q5.1 (G), R2.2
unnamed: J1.4, R3.2
unnamed: J1.6, U1.4
unnamed: J2.1, U1.3
unnamed: J2.2, R1.2
unnamed: F1.1, J4.1
unnamed: F2.1, J4.2
unnamed: J7.2, J8.2
unnamed: J8.1, K2.4
unnamed: J8.3, K2.3
unnamed: J9.1, K3.4
unnamed: J9.3, K3.3
unnamed: R1.1, U1.1
unnamed: R8.2, U1.6
